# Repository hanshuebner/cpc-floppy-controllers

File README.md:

# Amstrad/Schneider CPC floppy controllers

> :warning: **This is a work in progress**: Don't fabricate PCBs from these files yet!

This project started as attempt to clone the Vortex F1-D floppy
controller, which supports two 720k DSDD drives.  The desire was to
have a controller that can support four drives at the same time.  The
starting point was a capture of the original PCB into a schematic,
which can be found in the [original](original/) directory.

Multiple variants have been designed, but none of the designs in this
repository have been tested, don't fabricate any PCBs at this point!

# no-rom

The [no-rom](no-rom/) variant contains a revised, but wasteful address
decoder and no ROM socket.  It works to some extent, but the first
revisions contained multiple errors and required several patches.  The
version in this repository has the fixes applied, but was not yet
fabricated and tested.

# no-rom-cpld

The [no-rom-cpld](no-rom-cpld/) variant replaces the TTL chips with a
CPLD, reducing the part count significantly.

# rom-cpld

The [rom-cpld](rom-cpld/) variant adds a Flash ROM that can act as a universal
ROM box in addition to holding an operating system ROM to drive the
floppy disk controller.

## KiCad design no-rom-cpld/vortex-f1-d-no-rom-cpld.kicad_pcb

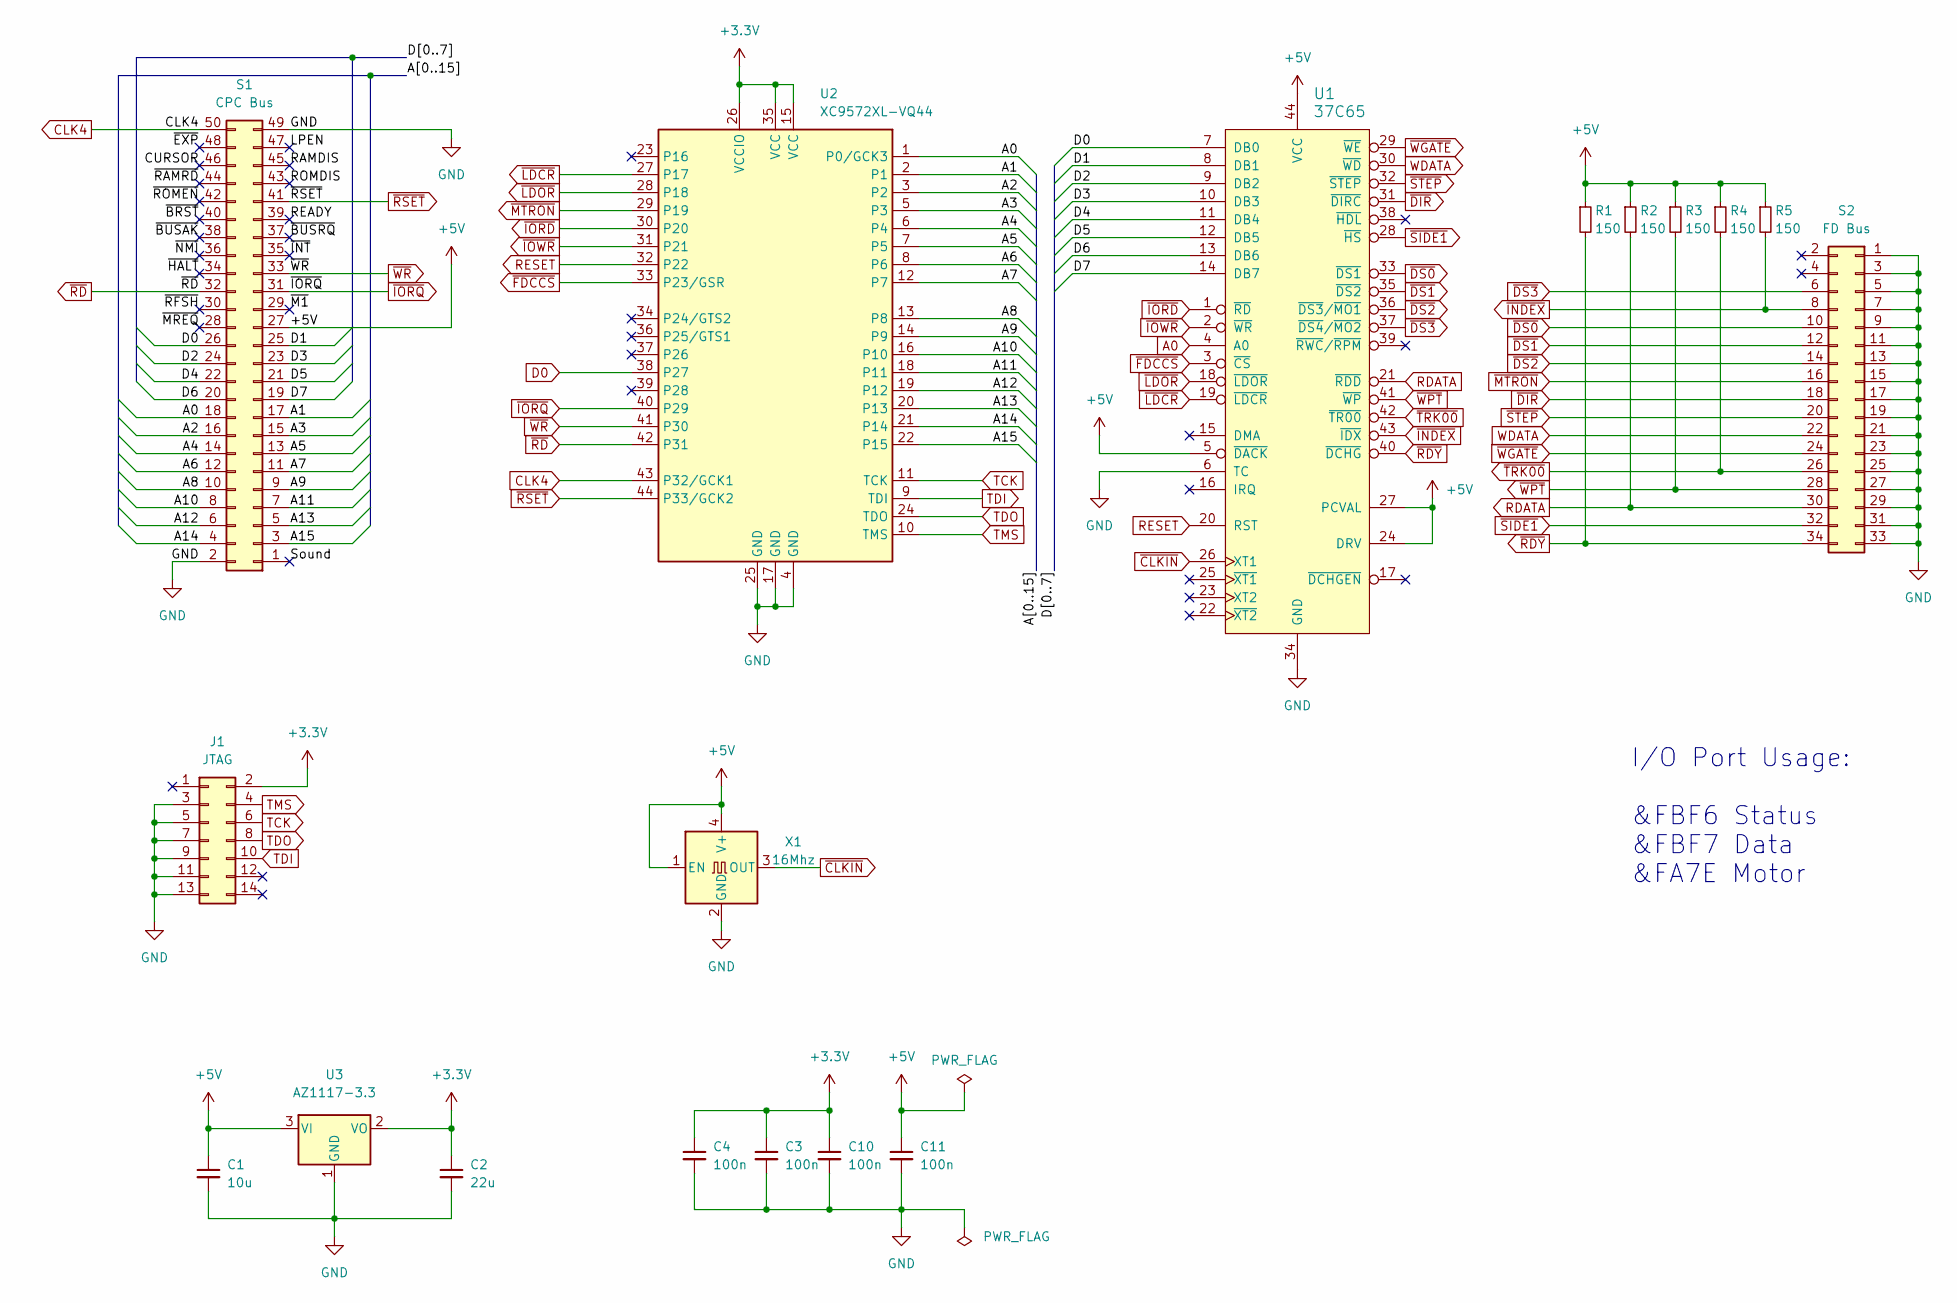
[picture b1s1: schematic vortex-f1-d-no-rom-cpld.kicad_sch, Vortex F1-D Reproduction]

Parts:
C1: 10u; C_0603_1608Metric_Pad1.08x0.95mm_HandSolder
C2: 22u; C_0603_1608Metric_Pad1.08x0.95mm_HandSolder
C3, C4, C10, C11: 100n; C_0603_1608Metric_Pad1.08x0.95mm_HandSolder
J1: JTAG; PinHeader_2x07_P2.00mm_Vertical
R1, R2, R3, R4, R5: 150; R_0603_1608Metric_Pad0.98x0.95mm_HandSolder
S1: CPC Bus; IDC-Header_2x25_P2.54mm_Horizontal
S2: FD Bus; IDC-Header_2x17_P2.54mm_Horizontal
U1: 37C65; PLCC-44
U2: XC9572XL-VQ44; TQFP-44_10x10mm_P0.8mm
U3: AZ1117-3.3; SOT-223-3_TabPin2
X1: 16Mhz; Oscillator_SMD_EuroQuartz_XO91-4Pin_7.0x5.0mm

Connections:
+3.3V: C2.1, C3.1, C4.1, C10.1, J1.2, U2.15 (VCC), U2.26 (VCCIO), U2.35 (VCC), U3.2 (VO)
+5V: C1.1, C11.1, R1.1, R2.1, R3.1, R4.1, R5.1, S1.27, U1.5 (~DACK), U1.24 (DRV), U1.27 (PCVAL), U1.44 (VCC), U3.3 (VI), X1.1 (EN), X1.4 (V+)
/A1: S1.17, U2.2 (P1)
/A2: S1.16, U2.3 (P2)
/A3: S1.15, U2.5 (P3)
/A4: S1.14, U2.6 (P4)
/A5: S1.13, U2.7 (P5)
/A6: S1.12, U2.8 (P6)
/A7: S1.11, U2.12 (P7)
/A8: S1.10, U2.13 (P8)
/A9: S1.9, U2.14 (P9)
/A10: S1.8, U2.16 (P10)
/A11: S1.7, U2.18 (P11)
/A12: S1.6, U2.19 (P12)
/A13: S1.5, U2.20 (P13)
/A14: S1.4, U2.21 (P14)
/A15: S1.3, U2.22 (P15)
/CURSOR: S1.46
/D1: S1.25, U1.8 (DB1)
/D2: S1.24, U1.9 (DB2)
/D3: S1.23, U1.10 (DB3)
/D4: S1.22, U1.11 (DB4)
/D5: S1.21, U1.12 (DB5)
/D6: S1.20, U1.13 (DB6)
/D7: S1.19, U1.14 (DB7)
/LPEN: S1.47
/RAMDIS: S1.45
/READY: S1.39
/ROMDIS: S1.43
/Sound: S1.1
/~BRST: S1.40
/~BUSAK: S1.38
/~BUSRQ: S1.37
/~EXP: S1.48
/~HALT: S1.34
/~INT: S1.35
/~M1: S1.29
/~MREQ: S1.28
/~NMI: S1.36
/~RAMRD: S1.44
/~RFSH: S1.30
/~ROMEN: S1.42
A0: S1.18, U1.4 (A0), U2.1 (P0/GCK3)
CLK4: S1.50, U2.43 (P32/GCK1)
D0: S1.26, U1.7 (DB0), U2.38 (P27)
GND: C1.2, C2.2, C3.2, C4.2, C10.2, C11.2, J1.3, J1.5, J1.7, J1.9, J1.11, J1.13, S1.2, S1.49, S2.1, S2.3, S2.5, S2.7, S2.9, S2.11, S2.13, S2.15, S2.17, S2.19, S2.21, S2.23, S2.25, S2.27, S2.29, S2.31, S2.33, U1.6 (TC), U1.34 (GND), U2.4 (GND), U2.17 (GND), U2.25 (GND), U3.1 (GND), X1.2 (GND)
RDATA: R2.2, S2.30, U1.21 (~RDD)
RESET: U1.20 (RST), U2.32 (P22)
TCK: J1.6, U2.11 (TCK)
TDI: J1.10, U2.9 (TDI)
TDO: J1.8, U2.24 (TDO)
TMS: J1.4, U2.10 (TMS)
WDATA: S2.22, U1.30 (~WD)
~CLKIN: U1.26 (XT1), X1.3 (OUT)
~DIR: S2.18, U1.31 (~DIRC)
~DS0: S2.10, U1.33 (~DS1)
~DS1: S2.12, U1.35 (~DS2)
~DS2: S2.14, U1.36 (~DS3/~MO1)
~DS3: S2.6, U1.37 (~DS4/~MO2)
~FDCCS: U1.3 (~CS), U2.33 (P23/GSR)
~INDEX: R5.2, S2.8, U1.43 (~IDX)
~IORD: U1.1 (~RD), U2.30 (P20)
~IORQ: S1.31, U2.40 (P29)
~IOWR: U1.2 (~WR), U2.31 (P21)
~LDCR: U1.19 (~LDCR), U2.27 (P17)
~LDOR: U1.18 (~LDOR), U2.28 (P18)
~RDY: R1.2, S2.34, U1.40 (~DCHG)
~RD: S1.32, U2.42 (P31)
~RSET: S1.41, U2.44 (P33/GCK2)
~SIDE1: S2.32, U1.28 (~HS)
~STEP: S2.20, U1.32 (~STEP)
~TRK00: R4.2, S2.26, U1.42 (~TR00)
~WGATE: S2.24, U1.29 (~WE)
~WPT: R3.2, S2.28, U1.41 (~WP)
~WR: S1.33, U2.41 (P30)

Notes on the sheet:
I/O Port Usage: &FBF6 Status &FBF7 Data &FA7E Motor

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
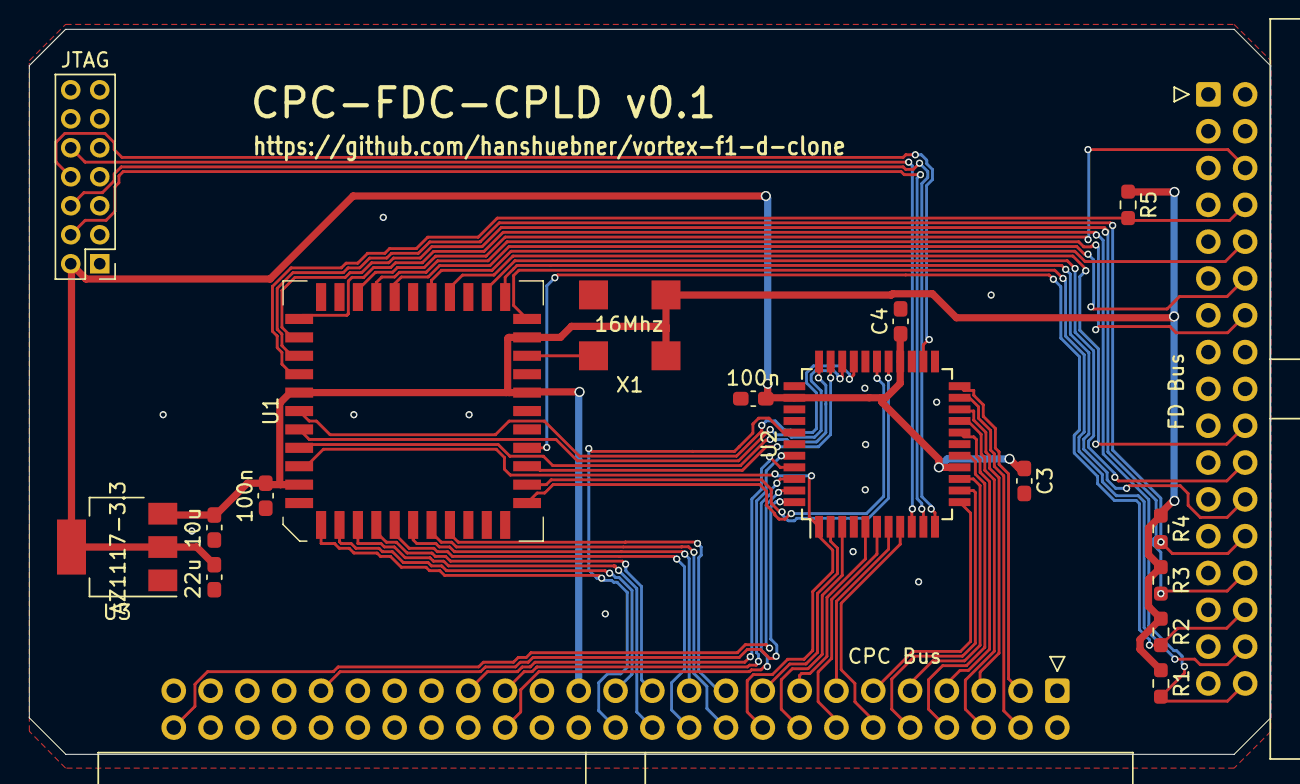
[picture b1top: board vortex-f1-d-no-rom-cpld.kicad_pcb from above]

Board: 2 copper layers, 85.6 x 50.0 mm, 18 parts (0 on the bottom side), 57 nets.

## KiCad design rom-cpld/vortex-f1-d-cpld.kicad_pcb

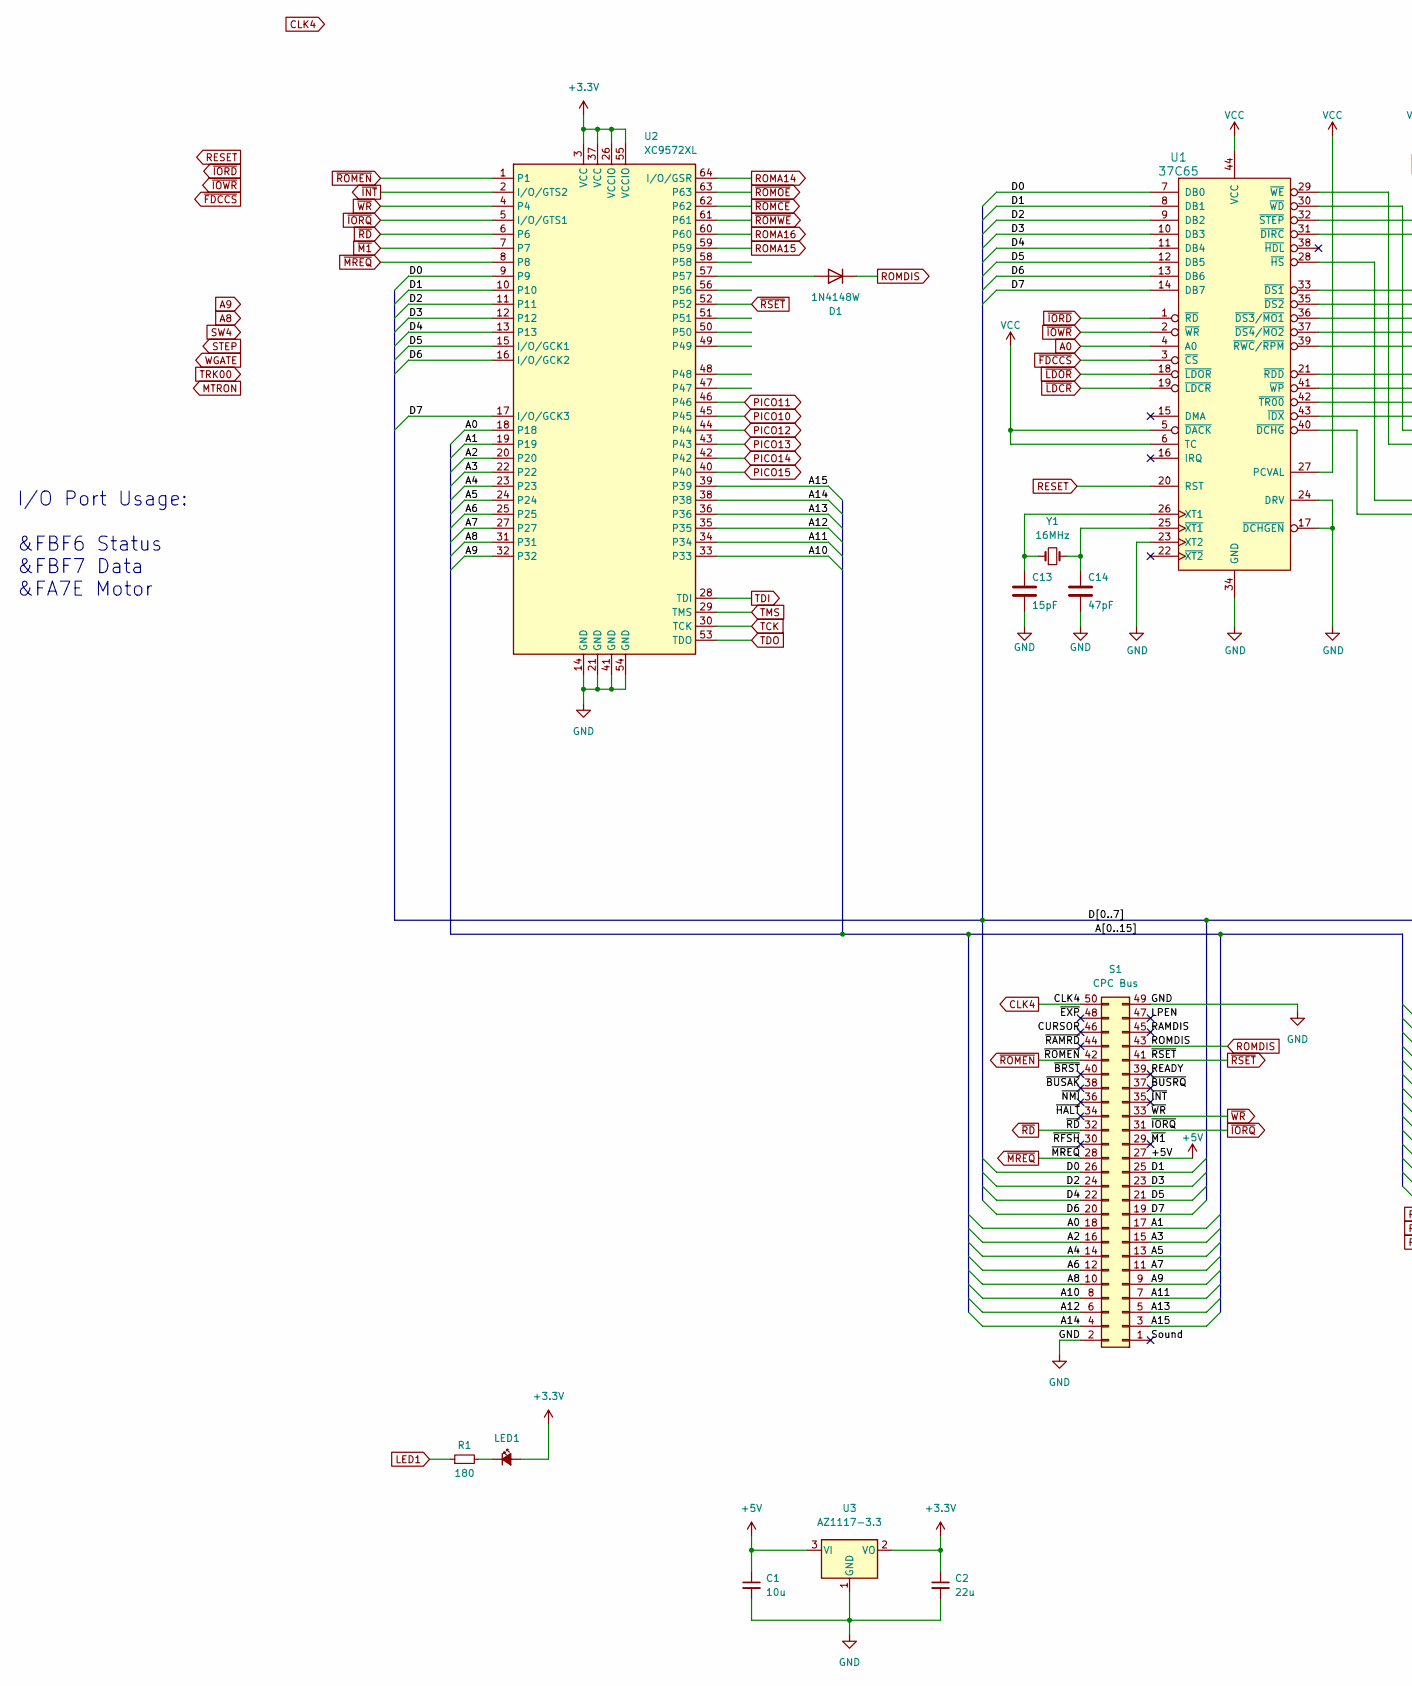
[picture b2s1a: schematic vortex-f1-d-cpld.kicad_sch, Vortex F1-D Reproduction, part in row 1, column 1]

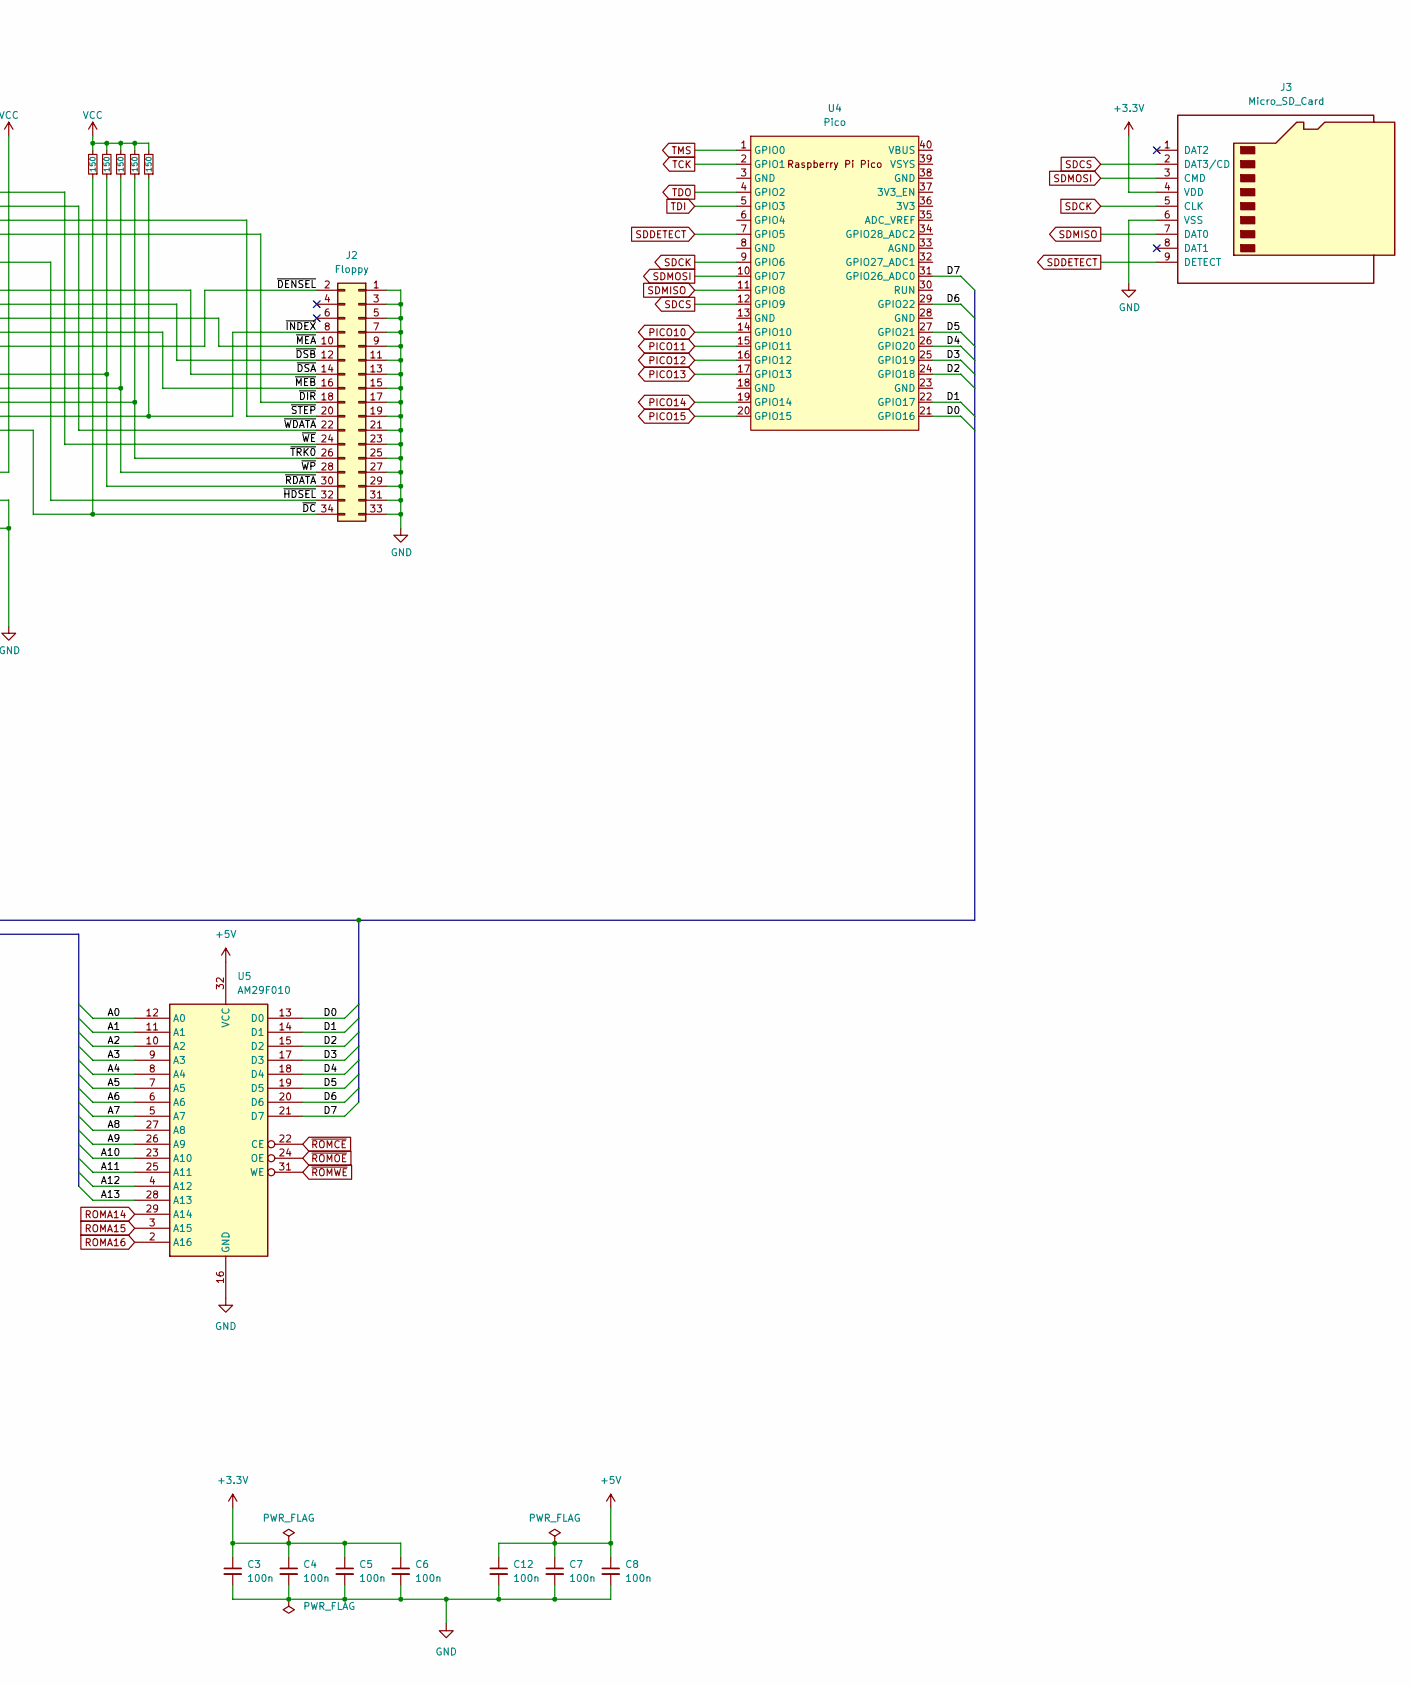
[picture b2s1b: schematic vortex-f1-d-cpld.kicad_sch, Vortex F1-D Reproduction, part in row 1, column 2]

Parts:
C1: 10u; C_0603_1608Metric_Pad1.08x0.95mm_HandSolder
C2: 22u; C_0603_1608Metric_Pad1.08x0.95mm_HandSolder
C3, C4, C5, C6, C7, C8, C12: 100n; C_0603_1608Metric_Pad1.08x0.95mm_HandSolder
C13: 15pF; C_0603_1608Metric_Pad1.08x0.95mm_HandSolder
C14: 47pF; C_0603_1608Metric_Pad1.08x0.95mm_HandSolder
D1: 1N4148W; D_SOD-123
J2: Floppy; PinHeader_2x17_P2.54mm_Horizontal
J3: Micro_SD_Card; J_SD_Card-micro_socket_A
LED1: STATUS; LED_0805_2012Metric_Pad1.15x1.40mm_HandSolder
R1: 180; R_0603_1608Metric_Pad0.98x0.95mm_HandSolder
R2, R3, R4, R5, R6: 150; R_0603_1608Metric_Pad0.98x0.95mm_HandSolder
S1: CPC Bus; IDC-Header_2x25_P2.54mm_Horizontal
U1: 37C65; PLCC-44
U2: XC9572XL; TQFP-64_10x10mm_P0.5mm
U3: AZ1117-3.3; SOT-223-3_TabPin2
U4: Pico; RPi_Pico_SMD_TH
U5: AM29F010; PLCC-32_11.4x14.0mm_P1.27mm
Y1: 16MHz; Crystal_SMD_7050-4Pin_7.0x5.0mm

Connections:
+3.3V: C2.1, C3.1, C4.1, C5.1, C6.1, J3.4 (VDD), LED1.2 (A), U2.3 (VCC), U2.26 (VCCIO), U2.37 (VCC), U2.55 (VCCIO), U3.2 (VO)
+5V: C1.1, C7.1, C8.1, C12.1, S1.27, U3.3 (VI), U5.32 (VCC)
/A1: S1.17, U2.19, U5.11 (A1)
/A2: S1.16, U2.20, U5.10 (A2)
/A3: S1.15, U2.22, U5.9 (A3)
/A4: S1.14, U2.23, U5.8 (A4)
/A5: S1.13, U2.24, U5.7 (A5)
/A6: S1.12, U2.25, U5.6 (A6)
/A7: S1.11, U2.27, U5.5 (A7)
/A10: S1.8, U2.33, U5.23 (A10)
/A11: S1.7, U2.34, U5.25 (A11)
/A12: S1.6, U2.35, U5.4 (A12)
/A13: S1.5, U2.36, U5.28 (A13)
/A14: S1.4, U2.38
/A15: S1.3, U2.39
/CURSOR: S1.46
/D0: S1.26, U1.7 (DB0), U2.9, U4.21 (GPIO16), U5.13 (D0)
/D1: S1.25, U1.8 (DB1), U2.10, U4.22 (GPIO17), U5.14 (D1)
/D2: S1.24, U1.9 (DB2), U2.11, U4.24 (GPIO18), U5.15 (D2)
/D3: S1.23, U1.10 (DB3), U2.12, U4.25 (GPIO19), U5.17 (D3)
/D4: S1.22, U1.11 (DB4), U2.13, U4.26 (GPIO20), U5.18 (D4)
/D5: S1.21, U1.12 (DB5), U2.15 (I/O/GCK1), U4.27 (GPIO21), U5.19 (D5)
/D6: S1.20, U1.13 (DB6), U2.16 (I/O/GCK2), U4.29 (GPIO22), U5.20 (D6)
/D7: S1.19, U1.14 (DB7), U2.17 (I/O/GCK3), U4.31 (GPIO26_ADC0), U5.21 (D7)
/LPEN: S1.47
/RAMDIS: S1.45
/READY: S1.39
/Sound: S1.1
/~BRST: S1.40
/~BUSAK: S1.38
/~BUSRQ: S1.37
/~DC: J2.34, R2.1, U1.40 (~DCHG)
/~DENSEL: J2.2, U1.39 (~RWC/~RPM)
/~DIR: J2.18, U1.31 (~DIRC)
/~DSA: J2.14, U1.33 (~DS1)
/~DSB: J2.12, U1.35 (~DS2)
/~EXP: S1.48
/~HALT: S1.34
/~HDSEL: J2.32, U1.28 (~HS)
/~INDEX: J2.8, R6.1, U1.43 (~IDX)
/~MEA: J2.10, U1.36 (~DS3/~MO1)
/~MEB: J2.16, U1.37 (~DS4/~MO2)
/~NMI: S1.36
/~RAMRD: S1.44
/~RDATA: J2.30, R3.1, U1.21 (~RDD)
/~RFSH: S1.30
/~STEP: J2.20, U1.32 (~STEP)
/~TRK0: J2.26, R5.1, U1.42 (~TR00)
/~WDATA: J2.22, U1.30 (~WD)
/~WE: J2.24, U1.29 (~WE)
/~WP: J2.28, R4.1, U1.41 (~WP)
A0: S1.18, U1.4 (A0), U2.18, U5.12 (A0)
A8: S1.10, U2.31, U5.27 (A8)
A9: S1.9, U2.32, U5.26 (A9)
CLK4: S1.50
GND: C1.2, C2.2, C3.2, C4.2, C5.2, C6.2, C7.2, C8.2, C12.2, C13.2, C14.2, J2.1, J2.3, J2.5, J2.7, J2.9, J2.11, J2.13, J2.15, J2.17, J2.19, J2.21, J2.23, J2.25, J2.27, J2.29, J2.31, J2.33, J3.6 (VSS), S1.2, S1.49, U1.17 (~DCHGEN), U1.23 (XT2), U1.24 (DRV), U1.34 (GND), U2.14 (GND), U2.21 (GND), U2.41 (GND), U2.54 (GND), U3.1 (GND), U5.16 (GND)
LED1: R1.1
unnamed: D1.2 (A), U2.57
unnamed: LED1.1 (K), R1.2
unnamed: C13.1, U1.26 (XT1), Y1.1
unnamed: C14.1, U1.25 (~XT1), Y1.2
PICO10: U2.45, U4.14 (GPIO10)
PICO11: U2.46, U4.15 (GPIO11)
PICO12: U2.44, U4.16 (GPIO12)
PICO13: U2.43, U4.17 (GPIO13)
PICO14: U2.42, U4.19 (GPIO14)
PICO15: U2.40, U4.20 (GPIO15)
RESET: U1.20 (RST)
ROMA14: U2.64 (I/O/GSR), U5.29 (A14)
ROMA15: U2.59, U5.3 (A15)
ROMA16: U2.60, U5.2 (A16)
ROMDIS: D1.1 (K), S1.43
SDCK: J3.5 (CLK), U4.9 (GPIO6)
SDCS: J3.2 (DAT3/CD), U4.12 (GPIO9)
SDDETECT: J3.9 (DETECT), U4.7 (GPIO5)
SDMISO: J3.7 (DAT0), U4.11 (GPIO8)
SDMOSI: J3.3 (CMD), U4.10 (GPIO7)
TCK: U2.30 (TCK), U4.2 (GPIO1)
TDI: U2.28 (TDI), U4.5 (GPIO3)
TDO: U2.53 (TDO), U4.4 (GPIO2)
TMS: U2.29 (TMS), U4.1 (GPIO0)
VCC: R2.2, R3.2, R4.2, R5.2, R6.2, U1.5 (~DACK), U1.6 (TC), U1.27 (PCVAL), U1.44 (VCC)
~FDCCS: U1.3 (~CS)
~INT: S1.35, U2.2 (I/O/GTS2)
~IORD: U1.1 (~RD)
~IORQ: S1.31, U2.5 (I/O/GTS1)
~IOWR: U1.2 (~WR)
~LDCR: U1.19 (~LDCR)
~LDOR: U1.18 (~LDOR)
~M1: S1.29, U2.7
~MREQ: S1.28, U2.8
~RD: S1.32, U2.6
~ROMCE: U2.62, U5.22 (CE)
~ROMEN: S1.42, U2.1
~ROMOE: U2.63, U5.24 (OE)
~ROMWE: U2.61, U5.31 (WE)
~RSET: S1.41, U2.52
~WR: S1.33, U2.4

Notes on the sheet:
I/O Port Usage: &FBF6 Status &FBF7 Data &FA7E Motor

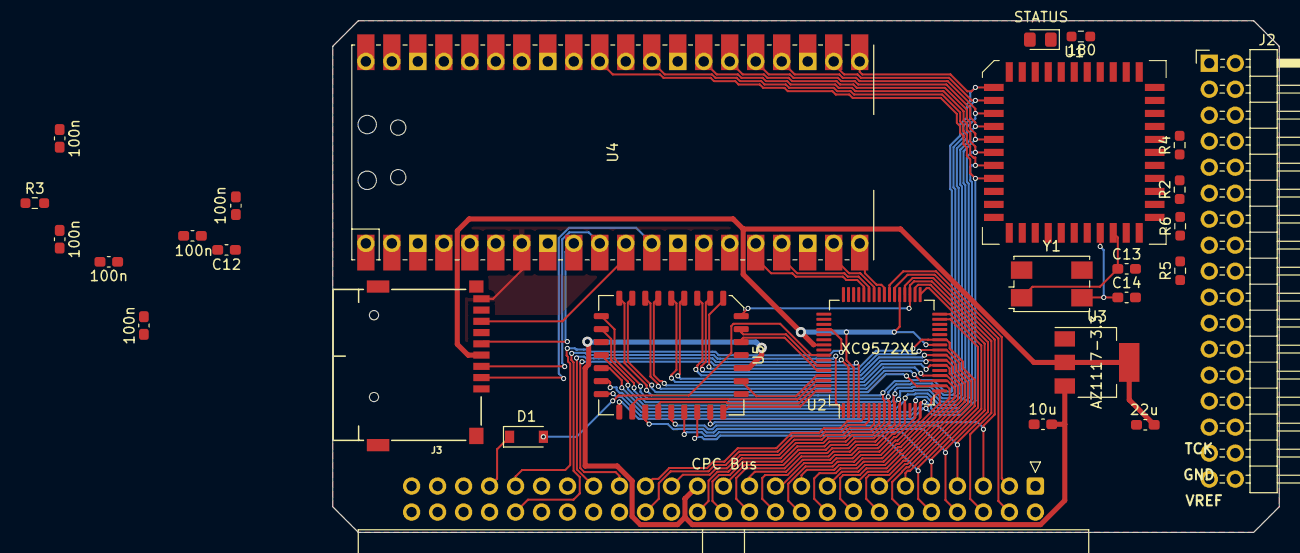
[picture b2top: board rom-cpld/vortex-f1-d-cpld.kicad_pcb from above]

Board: 2 copper layers, 92.5 x 50.0 mm, 28 parts (0 on the bottom side), 77 nets.

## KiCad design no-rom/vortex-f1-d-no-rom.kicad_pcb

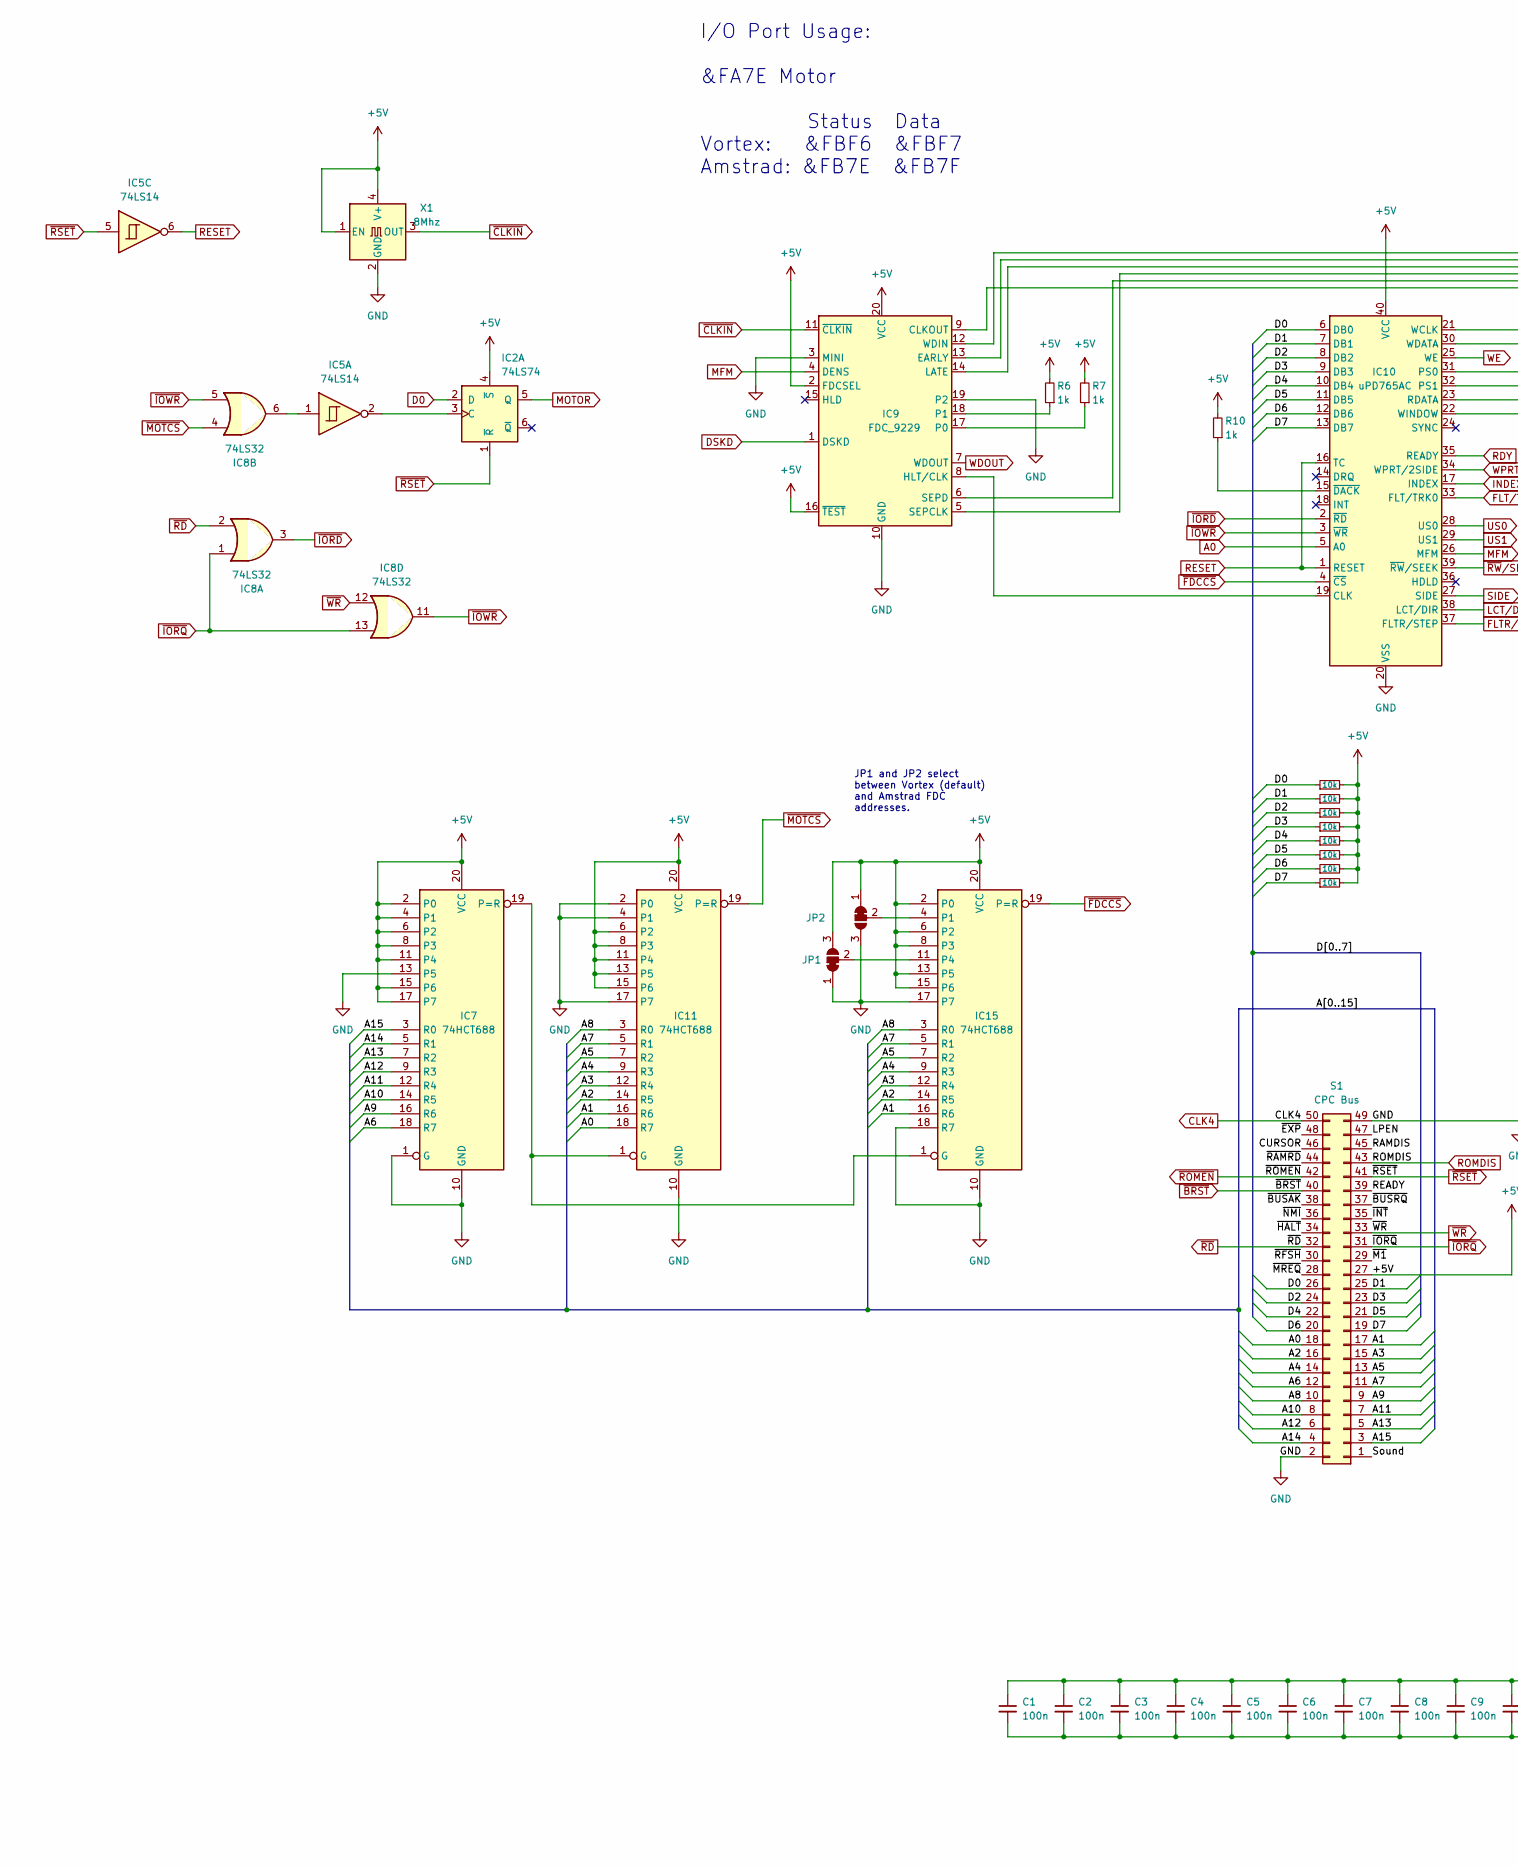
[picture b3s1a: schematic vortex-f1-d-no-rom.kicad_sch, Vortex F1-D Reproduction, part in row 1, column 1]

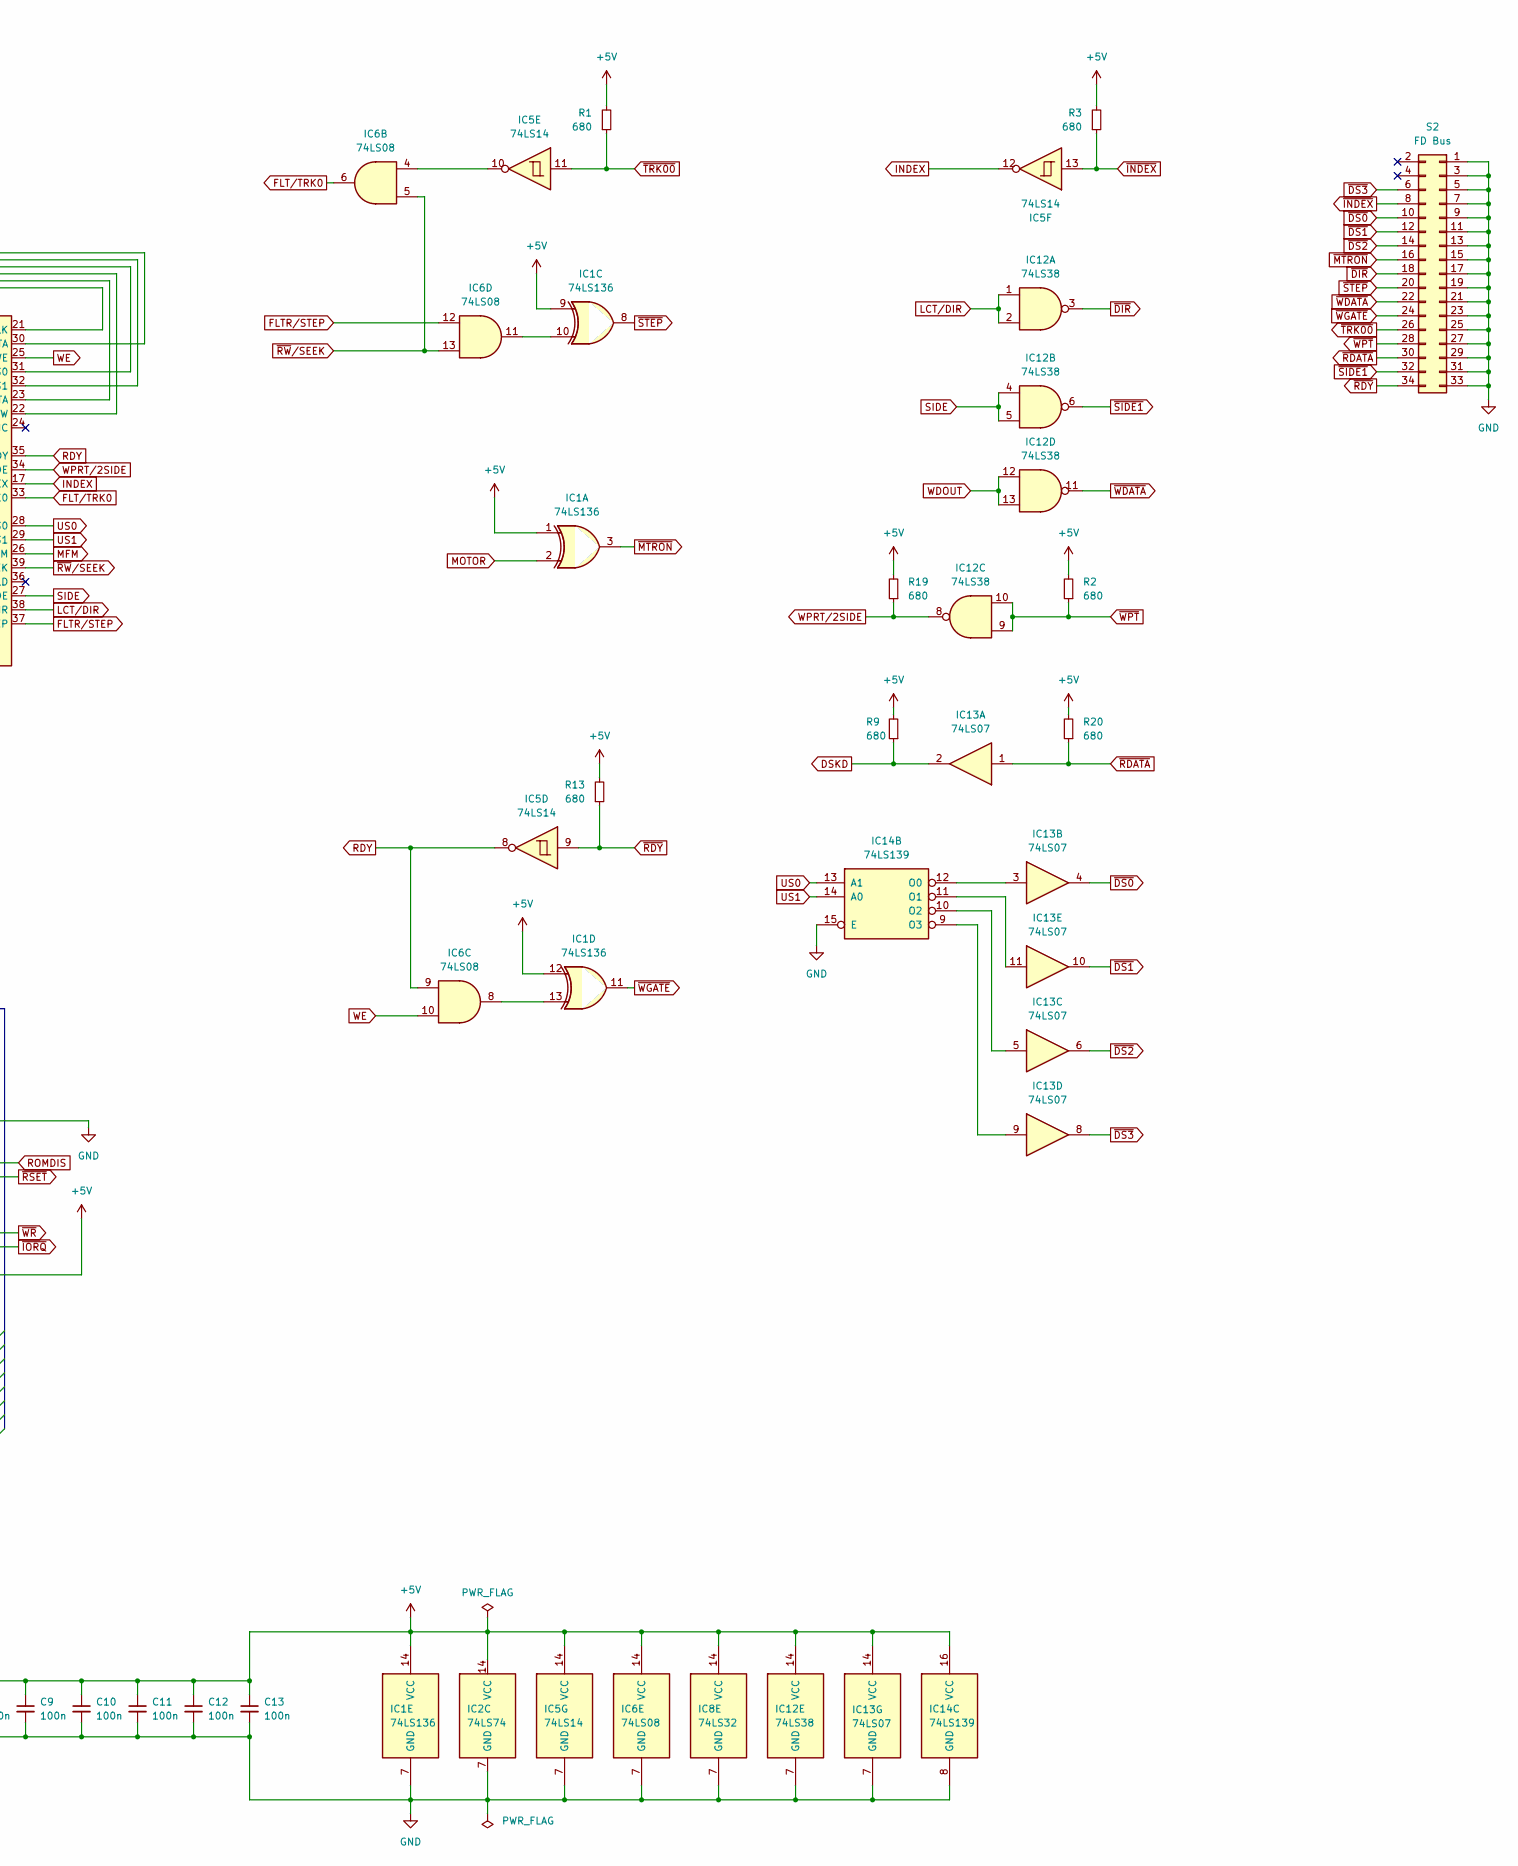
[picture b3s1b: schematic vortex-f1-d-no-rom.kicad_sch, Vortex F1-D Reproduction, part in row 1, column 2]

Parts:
C1, C2, C3, C4, C5, C6, C7, C8, C9, C10, C11, C12, C13: 100n; C_0603_1608Metric_Pad1.08x0.95mm_HandSolder
IC1: 74LS136; DIP-14_W7.62mm_Socket
IC2: 74LS74; DIP-14_W7.62mm_Socket
IC5: 74LS14; DIP-14_W7.62mm_Socket
IC6: 74LS08; DIP-14_W7.62mm_Socket
IC7, IC11, IC15: 74HCT688; DIP-20_W7.62mm_Socket
IC8: 74LS32; DIP-14_W7.62mm_Socket
IC9: FDC_9229; DIP-20_W7.62mm_Socket
IC10: uPD765AC; DIP-40_W15.24mm_Socket
IC12: 74LS38; DIP-14_W7.62mm_Socket
IC13: 74LS07; DIP-14_W7.62mm_Socket
IC14: 74LS139; DIP-16_W7.62mm_Socket
JP1: SolderJumper-3_P1.3mm_Bridged12_RoundedPad1.0x1.5mm
JP2: SolderJumper_3_Bridged12; SolderJumper-3_P1.3mm_Bridged12_RoundedPad1.0x1.5mm
R1, R2, R3, R9, R13, R19, R20: 680; R_0603_1608Metric_Pad0.98x0.95mm_HandSolder
R6, R7, R10: 1k; R_0603_1608Metric_Pad0.98x0.95mm_HandSolder
R8, R14, R17, R18, R23, R24, R25, R26: 10k; R_0603_1608Metric_Pad0.98x0.95mm_HandSolder
S1: CPC Bus; PinHeader_2x25_P2.54mm_Vertical
S2: FD Bus; IDC-Header_2x17_P2.54mm_Vertical
X1: 8Mhz; Oscillator_SMD_EuroQuartz_XO91-4Pin_7.0x5.0mm

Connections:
+5V: C1.1, C2.1, C3.1, C4.1, C5.1, C6.1, C7.1, C8.1, C9.1, C10.1, C11.1, C12.1, C13.1, IC1.1, IC1.9, IC1.12, IC1.14 (VCC), IC2.4 (~S), IC2.14 (VCC), IC5.14 (VCC), IC6.14 (VCC), IC7.2 (P0), IC7.4 (P1), IC7.6 (P2), IC7.8 (P3), IC7.11 (P4), IC7.15 (P6), IC7.17 (P7), IC7.20 (VCC), IC8.14 (VCC), IC9.2 (FDCSEL), IC9.16 (~TEST), IC9.20 (VCC), IC10.40 (VCC), IC11.6 (P2), IC11.8 (P3), IC11.11 (P4), IC11.13 (P5), IC11.15 (P6), IC11.20 (VCC), IC12.14 (VCC), IC13.14 (VCC), IC14.16 (VCC), IC15.2 (P0), IC15.6 (P2), IC15.8 (P3), IC15.13 (P5), IC15.15 (P6), IC15.20 (VCC), JP1.3 (B), JP2.1 (A), R1.2, R2.2, R3.2, R6.2, R7.2, R8.2, R9.2, R10.2, R13.2, R14.2, R17.2, R18.2, R19.2, R20.2, R23.2, R24.2, R25.2, R26.2, S1.27, X1.1 (EN), X1.4 (V+)
/A1: IC11.16 (R6), IC15.16 (R6), S1.17
/A2: IC11.14 (R5), IC15.14 (R5), S1.16
/A3: IC11.12 (R4), IC15.12 (R4), S1.15
/A4: IC11.9 (R3), IC15.9 (R3), S1.14
/A5: IC11.7 (R2), IC15.7 (R2), S1.13
/A6: IC7.18 (R7), S1.12
/A7: IC11.5 (R1), IC15.5 (R1), S1.11
/A8: IC11.3 (R0), IC15.3 (R0), S1.10
/A9: IC7.16 (R6), S1.9
/A10: IC7.14 (R5), S1.8
/A11: IC7.12 (R4), S1.7
/A12: IC7.9 (R3), S1.6
/A13: IC7.7 (R2), S1.5
/A14: IC7.5 (R1), S1.4
/A15: IC7.3 (R0), S1.3
/CURSOR: S1.46
/D1: IC10.7 (DB1), R14.1, S1.25
/D2: IC10.8 (DB2), R17.1, S1.24
/D3: IC10.9 (DB3), R18.1, S1.23
/D4: IC10.10 (DB4), R23.1, S1.22
/D5: IC10.11 (DB5), R24.1, S1.21
/D6: IC10.12 (DB6), R25.1, S1.20
/D7: IC10.13 (DB7), R26.1, S1.19
/LPEN: S1.47
/RAMDIS: S1.45
/READY: S1.39
/Sound: S1.1
/~BUSAK: S1.38
/~BUSRQ: S1.37
/~EXP: S1.48
/~HALT: S1.34
/~INT: S1.35
/~M1: S1.29
/~MREQ: S1.28
/~NMI: S1.36
/~RAMRD: S1.44
/~RFSH: S1.30
A0: IC10.5 (A0), IC11.18 (R7), S1.18
CLK4: S1.50
D0: IC2.2 (D), IC10.6 (DB0), R8.1, S1.26
DSKD: IC9.1 (DSKD), IC13.2, R9.1
FLTR/STEP: IC6.12, IC10.37 (FLTR/STEP)
FLT/TRK0: IC6.6, IC10.33 (FLT/TRK0)
GND: C1.2, C2.2, C3.2, C4.2, C5.2, C6.2, C7.2, C8.2, C9.2, C10.2, C11.2, C12.2, C13.2, IC1.7 (GND), IC2.7 (GND), IC5.7 (GND), IC6.7 (GND), IC7.1 (G), IC7.10 (GND), IC7.13 (P5), IC8.7 (GND), IC9.3 (MINI), IC9.10 (GND), IC9.19 (P2), IC10.20 (VSS), IC11.2 (P0), IC11.4 (P1), IC11.10 (GND), IC11.17 (P7), IC12.7 (GND), IC13.7 (GND), IC14.8 (GND), IC14.15 (E), IC15.10 (GND), IC15.17 (P7), IC15.18 (R7), JP1.1 (A), JP2.3 (B), S1.2, S1.49, S2.1, S2.3, S2.5, S2.7, S2.9, S2.11, S2.13, S2.15, S2.17, S2.19, S2.21, S2.23, S2.25, S2.27, S2.29, S2.31, S2.33, X1.2 (GND)
INDEX: IC5.12, IC10.17 (INDEX)
LCT/DIR: IC10.38 (LCT/DIR), IC12.1, IC12.2
MFM: IC9.4 (DENS), IC10.26 (MFM)
MOTOR: IC1.2, IC2.5 (Q)
unnamed: IC1.10, IC6.11
unnamed: IC1.13, IC6.8
unnamed: IC2.3 (C), IC5.2
unnamed: IC5.1, IC8.6
unnamed: IC5.10, IC6.4
unnamed: IC9.17 (P0), R7.1
unnamed: IC9.18 (P1), R6.1
unnamed: IC9.8 (HLT/CLK), IC10.19 (CLK)
unnamed: IC9.14 (LATE), IC10.31 (PS0)
unnamed: IC9.13 (EARLY), IC10.32 (PS1)
unnamed: IC9.6 (SEPD), IC10.23 (RDATA)
unnamed: IC9.9 (CLKOUT), IC10.21 (WCLK)
unnamed: IC9.12 (WDIN), IC10.30 (WDATA)
unnamed: IC9.5 (SEPCLK), IC10.22 (WINDOW)
unnamed: IC10.15 (~DACK), R10.1
unnamed: IC7.19 (P=R), IC11.1 (G), IC15.1 (G)
unnamed: IC13.3, IC14.12 (O0)
unnamed: IC13.11, IC14.11 (O1)
unnamed: IC13.5, IC14.10 (O2)
unnamed: IC13.9, IC14.9 (O3)
unnamed: IC15.4 (P1), JP2.2 (C)
unnamed: IC15.11 (P4), JP1.2 (C)
RDY: IC5.8, IC6.9, IC10.35 (READY)
RESET: IC5.6, IC10.1 (RESET), IC10.16 (TC)
ROMDIS: S1.43
SIDE: IC10.27 (SIDE), IC12.4, IC12.5
US0: IC10.28 (US0), IC14.13 (A1)
US1: IC10.29 (US1), IC14.14 (A0)
WDOUT: IC9.7 (WDOUT), IC12.12, IC12.13
WE: IC6.10, IC10.25 (WE)
WPRT/2SIDE: IC10.34 (WPRT/2SIDE), IC12.8, R19.1
~BRST: S1.40
~CLKIN: IC9.11 (~CLKIN), X1.3 (OUT)
~DIR: IC12.3, S2.18
~DS0: IC13.4, S2.10
~DS1: IC13.10, S2.12
~DS2: IC13.6, S2.14
~DS3: IC13.8, S2.6
~FDCCS: IC10.4 (~CS), IC15.19 (P=R)
~INDEX: IC5.13, R3.1, S2.8
~IORD: IC8.3, IC10.2 (~RD)
~IORQ: IC8.1, IC8.13, S1.31
~IOWR: IC8.5, IC8.11, IC10.3 (~WR)
~MOTCS: IC8.4, IC11.19 (P=R)
~MTRON: IC1.3, S2.16
~RDATA: IC13.1, R20.1, S2.30
~RDY: IC5.9, R13.1, S2.34
~RD: IC8.2, S1.32
~ROMEN: S1.42
~RSET: IC2.1 (~R), IC5.5, S1.41
~RW/SEEK: IC6.5, IC6.13, IC10.39 (~RW/SEEK)
~SIDE1: IC12.6, S2.32
~STEP: IC1.8, S2.20
~TRK00: IC5.11, R1.1, S2.26
~WDATA: IC12.11, S2.22
~WGATE: IC1.11, S2.24
~WPT: IC12.9, IC12.10, R2.1, S2.28
~WR: IC8.12, S1.33

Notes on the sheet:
JP1 and JP2 select between Vortex (default) and Amstrad FDC addresses.
I/O Port Usage: &FA7E Motor Status Data Vortex: &FBF6 &FBF7 Amstrad: &FB7E &FB7F
